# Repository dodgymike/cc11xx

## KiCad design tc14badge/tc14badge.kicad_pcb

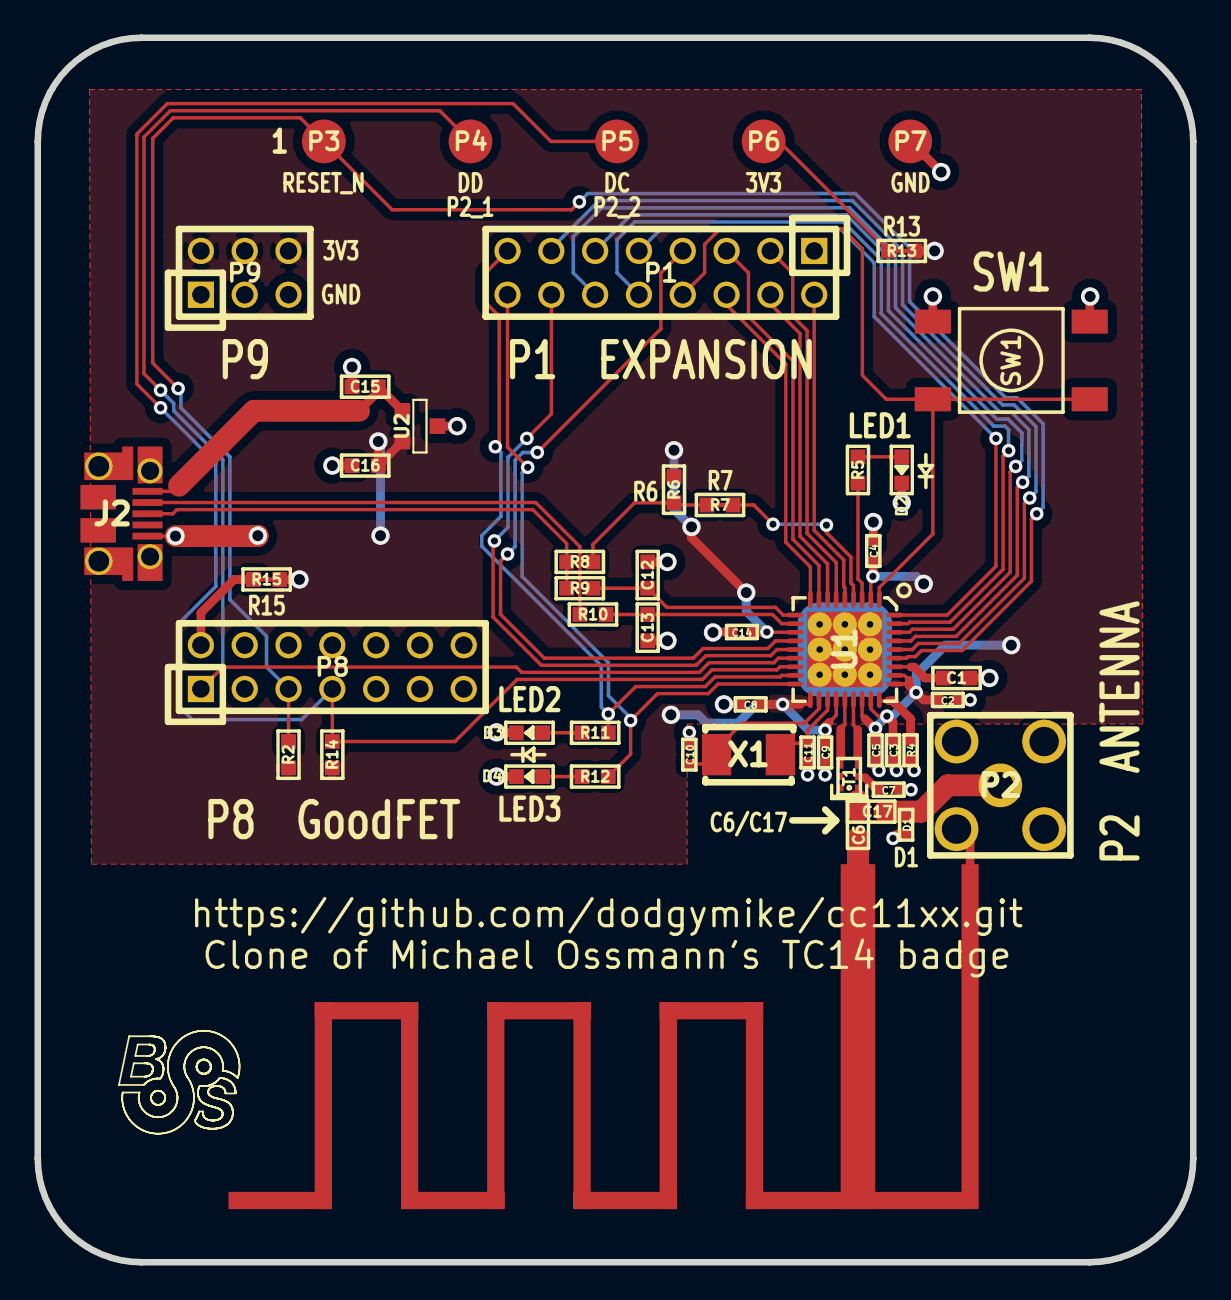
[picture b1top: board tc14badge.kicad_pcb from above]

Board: 2 copper layers, 67.0 x 71.0 mm, 50 parts (0 on the bottom side), 43 nets.

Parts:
C1, C15: 1uF; GSG-0603
C2, C4, C14: 100nF; GSG-0402
C3: 220pF; GSG-0402
C5, C7, C8: 10nF; GSG-0402
C6, C17: 10nF; GSG-0603
C9: 2p2; GSG-0402
C10, C11: 22pF; GSG-0402
C12, C13: 47pF; GSG-0603
C16: 4u7; GSG-0603
D1: TVS_DIODE; GSG-0402
D2: LED1; GSG-0603D
D3: LED2; GSG-0603D
D4: LED3; GSG-0603D
J1: GSG-900MHZ-F-ANTENNA; GSG-900MHZ-INVERTED-F
J2: GSG-USB-MICRO-B; GSG-USB-MICROB-FCI-10103594
P1: EXPANSION; GSG-HEADER-2x8
P2: ANTENNA; GSG-SMA-VERTICAL
P3: RESET_N; GSG-TESTPOINT-100MIL
P4: DD; GSG-TESTPOINT-100MIL
P5: DC; GSG-TESTPOINT-100MIL
P6: 3V3; GSG-TESTPOINT-100MIL
P7: GND; GSG-TESTPOINT-100MIL
P8: GOODFET; GSG-HEADER-2x7
P9: PWR; GSG-HEADER-2x3
R2, R14: 10k; GSG-0603
R4: 56k; GSG-0402
R5, R11, R12: 330; GSG-0603
R6: 0; GSG-0603
R7, R13, R15: 0; GSG-0603-SHORT-10MIL
R8: 1k5; GSG-0603
R9, R10: 33; GSG-0603
SW1: SW_PUSH; GSG-SPST-FSM4JSMATR
T1: BALUN; GSG-B0310J50100AHF
U1: CC1111; GSG-QFN36
U2: AP7313; GSG-SOT23-3
X1: CRYSTAL; GSG-XTAL-TXC-7A

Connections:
3V3: C2.1, C3.2, C4.2, C5.2, C8.2, C9.2, C14.2, C16.1, P9.2, P9.4, P9.6, R2.2, R6.2, R13.1, R14.1, R15.2, U1.2, U1.12, U1.19, U1.22, U1.25, U1.26, U1.28, U1.29, U2.2
/DC: P5.1, P8.7, R14.2, U1.16
/DD: P4.1, P8.1, U1.15
/P0_0: P1.2, U1.5
/P0_1: P1.3, U1.6
/P0_2: P1.4, U1.7
/P0_3: P1.5, U1.8
/P0_4: P1.6, U1.9
/P0_5: P1.7, U1.13
/P1_2: P1.8, SW1.1, U1.1
/P1_3: P1.9, U1.36
/P1_4: P1.10, U1.35
/P1_5: P1.11, U1.34
/P1_6: P1.12, U1.33
/P1_7: P1.13, U1.32
/P2_0: P1.14, U1.14
/P2_3: P1.15, R11.2, U1.17
/P2_4: P1.16, R12.2, U1.18
/RESET_N: P3.1, P8.5, R2.1, U1.31
/VBUS: C15.1, J2.1, U2.1
GND: C1.1, C2.2, C3.1, C4.1, C5.1, C7.2, C8.1, C9.1, C10.2, C11.2, C12.1, C13.1, C14.1, C15.2, C16.2, D1.1, D2.2, D3.2, D4.2, J1.2, J2.5, P1.1, P2.2, P2.3, P2.4, P2.5, P7.1, P8.9, P9.1, P9.3, P9.5, R4.2, SW1.2, U1.0, U2.3
unnamed: P6.1, R13.2
unnamed: C17.1, D1.2, P2.1
unnamed: D3.1, R11.1
unnamed: D4.1, R12.1
unnamed: T1.4, U1.23
unnamed: T1.3, U1.24
unnamed: C7.1, T1.2
unnamed: C6.2, J1.1
unnamed: C6.1, C17.2, T1.1
unnamed: C1.2, U1.30
unnamed: R7.2, U1.4
unnamed: R6.1, R7.1, R8.2
unnamed: D2.1, R5.1
unnamed: P8.2, R15.1
unnamed: J2.2, R10.1
unnamed: C12.2, R9.2, U1.10
unnamed: J2.3, R8.1, R9.1
unnamed: C11.1, U1.21, X1.2
unnamed: R4.1, U1.27
unnamed: C10.1, U1.20, X1.1
unnamed: R5.2, U1.3
unnamed: C13.2, R10.2, U1.11

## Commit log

2017-06-19 Converted to new kicad format + made board smaller
2017-06-19 Added BSides and defcon icons to silkscreen + generated gerbers for prod run
2017-06-22 Removed Defcon smiley pirate logo
2017-06-22 Latest Gerber
